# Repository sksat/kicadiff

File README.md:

# kicadiff

Visual diff tool for KiCad projects — see what changed between two
states of a `.kicad_pcb` / `.kicad_sch` / `.kicad_sym` / `.kicad_mod`
file in your browser, or as a markdown report you can paste into a PR.

[日本語版 README](./README.ja.md)

## What you get

- **HTML viewer** with side-by-side / overlay / swipe modes, layer toggles
  for PCBs, page navigation for hierarchical schematics, wheel-to-zoom and
  right-click-drag-to-pan, and an amber tab marker on files / pages whose
  rendered output actually changed.
- **Markdown report** (`--md`) with side-by-side image tables and a
  structural component diff (added / removed / changed by reference
  designator), plus — for PCBs — a `Nets` subsection that lists added /
  removed nets and pads that were rewired (`R1.2: GND → /VCC`). Pad
  transitions to or from the unconnected net are surfaced too
  (`R7.1: (unconnected) → +3V3`). Both legacy (`(net id "name")`) and
  KiCad 10 (`(net "name")`, no top-level net table) shapes are
  supported. Good for PR descriptions and commit messages.
- **Text-only structural diff** (`--text-only`) — fast, no image
  rendering, prints to stdout. Includes the same `Nets` subsection for
  PCBs so routing changes show up in CI logs and grep:

  ```
  blink.kicad_pcb (pcb): +0 -0 ~1 =3
    ~ R1  value: 330 → 470
    Nets: +1 -0 ~2
      + /LED_OUT
      ~ R1.2: GND → /LED_OUT
      ~ R7.1: (unconnected) → +3V3
  ```
- **DRC / ERC violation diff** (`kicadiff check`) — runs design-rule and
  electrical-rule checks on both sides and reports the delta as
  `+N new / -M fixed / =K unchanged`. Exits 1 when the target side
  introduces NEW violations (non-zero on operational failures too —
  missing `kicad-cli`, git errors, JSON parse errors), so it makes a
  good PR gate that fails on regressions while ignoring pre-existing
  findings.

## Requirements

- [`kicad-cli`](https://www.kicad.org/) 9.x or later (rendering engine).
- [Bun](https://bun.sh) — runs the TypeScript CLI directly via shebang.
  Bun also compiles the standalone binary, so no separate Node install
  is needed for any workflow. Standalone binary users skip this.

The render pipeline (SVG → PNG, tri-colour pixel diff highlight) used to
need `rsvg-convert` and ImageMagick; both are now in-process
(`@resvg/resvg-js` for rasterisation, a small custom classifier on top
of `pngjs` for the diff overlay).

## Install

Three ways depending on what's already on your machine:

```sh
# 1. One-shot via Bun's package runner (no install)
bunx kicadiff [args...]

# 2. Global install (puts `kicadiff` on PATH)
pnpm add -g kicadiff
# or with `bun add -g kicadiff` / `npm install -g kicadiff`

# 3. Standalone binary — single file, no Bun runtime needed.
#    Drops `kicadiff` into ~/.local/bin (override with KICADIFF_INSTALL_DIR).
curl -fsSL https://raw.githubusercontent.com/sksat/kicadiff/main/install.sh | sh
```

`kicad-cli` (and `rsvg-convert` / `magick`) are not bundled — install KiCad 9+
first, then pick whichever kicadiff distribution form fits your workflow.

## Usage

`kicadiff` works on the same positional argument shape as `git diff`,
plus a few subcommands when you want to scope to one file type.

```sh
# Project-level diff (cwd, both PCB and schematic, default = index vs working
# tree — same as `git diff`)
kicadiff

# Pass a project root, a .kicad_pro, or any single KiCad file
kicadiff path/to/project/
kicadiff project.kicad_pro
kicadiff project.kicad_pcb

# Staged changes only (same as `git diff --cached` / `git diff --staged`)
kicadiff --cached project/
kicadiff --staged project/             # alias

# Compare arbitrary refs
kicadiff HEAD path/to/project/         # working tree vs HEAD (includes staged)
kicadiff main path/to/project/         # working tree vs main
kicadiff v1.0 v2.0 board.kicad_pcb     # v1.0 vs v2.0
kicadiff main..feat foo.kicad_pcb      # range syntax
kicadiff main -- foo.kicad_pcb         # explicit `--` separator
kicadiff :0 project/                   # explicit index ref (alias: index / staged)

# Subcommands scope to one file type (skip sibling auto-detect)
kicadiff pcb foo.kicad_pcb
kicadiff sch foo.kicad_sch       # alias: schematic
kicadiff sym lib.kicad_sym       # alias: symbol
kicadiff fp foo.kicad_mod        # alias: footprint
kicadiff fp lib.pretty           # whole .pretty/ library

# Output formats
kicadiff project/                       # default: HTML viewer + images
kicadiff project/ --md                  # markdown report + images, no HTML
kicadiff project/ --md --output report.md
kicadiff project/ --md --output -       # markdown to stdout, logs to stderr
kicadiff project/ --text                # also print structural text diff
kicadiff project/ --text-only           # text only, skip rendering (fast)
kicadiff project/ --images-only         # PNGs only, no HTML / markdown

# Custom markdown templates (Mustache subset: {{var}}, {{#section}}…{{/section}},
# {{^inverted}}…{{/inverted}}). Project template sees from_label / to_label /
# file_count / has_changes / files / file_sections. File template sees path /
# type / before_image / after_image / has_both / after_only / before_only /
# added_count / removed_count / changed_count / unchanged_count /
# nets_added / nets_removed / nets_changed (pcb only) /
# has_structural_diff (real component OR net changes) / has_visual_diff (PNGs
# differ) / has_changes (any of the above) / structural_diff (formatted body). Either
# flag is optional; the default template ships built-in.
kicadiff project/ --md --md-template my-report.md.tpl
kicadiff project/ --md --md-file-template my-file.md.tpl

# Auto-open the HTML in VSCode (Live Preview), a browser, etc.
kicadiff project/ --open vscode
kicadiff project/ --open firefox
kicadiff project/ --open=/usr/bin/open  # arbitrary command

# Watch mode — re-render every time an input file changes. Hot reload comes
# from the viewer: VSCode Live Preview / live-server / similar will refresh
# the page automatically once kicadiff overwrites the images. For plain
# file:// browsers, kicadiff injects a tiny image-polling script so the
# rendered images update in place without needing F5.
kicadiff project/ --watch
kicadiff project/ --watch --open vscode

# Other
kicadiff project/ -v                    # verbose summary (full PNG paths)
kicadiff project/ -q                    # suppress summary
kicadiff project/ --no-cache            # bypass the render cache
kicadiff project/ --exit-code           # exit 1 if any change (mirrors `git diff --exit-code`)

# Claude Code PostToolUse hook integration. Reads the hook JSON from
# stdin, renders only when the edited file is .kicad_pcb / .kicad_sch.
# Default: --open vscode (override with --open <target> as usual).
kicadiff hook

# DRC / ERC violation diff — third fast-path mode alongside --text-only.
# Runs `kicad-cli pcb drc` (PCB) / `kicad-cli sch erc` (schematic) on both
# sides and reports the delta as +N new / -M fixed / =K unchanged. Exits 1
# when NEW violations are introduced on the target side; pre-existing
# violations that persist do not fail the gate. Operational failures
# (missing kicad-cli, git errors, JSON parse errors) also produce a
# non-zero exit. Useful as a PR gate that fails only on regressions,
# independent of any visual diff.
kicadiff check                          # PCB+sch in cwd, index vs working
kicadiff check HEAD project/            # working tree vs HEAD
kicadiff check main..feat foo.kicad_pcb # main vs feat, PCB only
```

## Output

By default kicadiff writes to `<repo>/.claude/preview/` (next to the git
root) so the directory is easy to find from the project. Override with
`--output-dir <dir>` for the image directory, and `--output <path>` to
relocate the HTML / markdown file specifically (image paths in the
file get rewritten to be relative to it, so the file stays portable).

The HTML viewer is a single file with the manifest + image references
inline; you can email it, host it as a static asset, or open it
locally with VSCode's Live Preview extension.

## Render cache

Every per-side render is content-addressed and cached under
`$XDG_CACHE_HOME/kicadiff` (or `~/.cache/kicadiff`). Repeat runs
against unchanged content return in ~1 s vs ~5 s cold. Bypass with
`--no-cache` or override the location with `KICADIFF_CACHE_DIR`.

The cache grows monotonically — every kicad-cli version bump and every
content edit adds a new entry, and nothing is evicted automatically.
Inspect and reclaim space with the `cache` subcommand:

```sh
# Show cache directory, entry count, total size, and oldest / newest age
kicadiff cache stats

# Delete entries older than a cutoff (units: s/m/h/d, unit required)
kicadiff cache prune --older-than 30d
kicadiff cache prune --older-than 30d --dry-run    # preview, change nothing

# Wipe the whole cache (recursive rm of the cache root — any stray files
# at the root go too, not just registered entries). `--yes` skips the
# confirmation prompt and is required in non-TTY (CI) environments so
# the prompt can never hang a build. As a safety net, `--all` refuses
# to run unless the cache root contains a `.kicadiff-cache` marker
# (auto-dropped on first cache write and on any `cache stats` /
# read) — that way a misconfigured `KICADIFF_CACHE_DIR` can't silently
# wipe an unrelated directory. For a pre-existing cache from before
# this marker was introduced, run `kicadiff cache stats` once to
# install the marker, then retry `--all`. Use `rm -rf` manually if
# you really mean to delete such a directory.
#
# Note: `cache stats` does NOT recurse into foreign top-level
# directories (anything whose name doesn't match the cache layout's
# 2-char hex bucket pattern). Their bytes are excluded from "Total
# size" — a misconfigured `KICADIFF_CACHE_DIR` (e.g. `$HOME`) won't
# make `stats` walk a huge unrelated tree. `--all` will still wipe
# the entire cache root, so it may reclaim more than `stats` reports.
kicadiff cache prune --all --yes
```

## GitHub Actions

Drop the action into a workflow to render a visual diff for every PR
that touches a KiCad file. The action handles KiCad install, runs
kicadiff, and (opt-in) uploads the rendered images as a build artifact,
writes a job summary with inline before/after images, upserts a sticky
PR comment, and updates a marked section in the PR description.

```yaml
# .github/workflows/kicad-diff.yml
name: KiCad visual diff
on:
  pull_request:
    paths: ["**/*.kicad_pcb", "**/*.kicad_sch"]
permissions:
  contents: read
  pull-requests: write   # only needed for pr-comment / pr-description
jobs:
  diff:
    runs-on: ubuntu-latest
    steps:
      - uses: actions/checkout@v6
        with: { fetch-depth: 0 }
      - uses: sksat/kicadiff@v0.2.0
        with:
          path: hardware/main-board   # default: cwd
          upload-artifact: 'true'
          pr-comment:      'true'
          pr-description:  'true'
```

Job summary embeds combined PNGs as base64 data URIs (no extra hosting
needed) up to a 1 MiB cap; if a project's images would overflow, the
action drops the rest, emits `::warning::`, and links to the artifact
for the full set. PR comment / description are kept text-only and link
to the artifact for images.

`install-kicadiff: bunx` (default) pulls the latest published kicadiff
on demand; pin a version with `install-kicadiff: <semver>`. Pre-installed
on PATH? Use `install-kicadiff: skip`.

## More

- `DESIGN.md` — architecture, render pipeline, cache key shape,
  manifest schema, viewer mode semantics
- `examples/blink/` — minimal KiCad project used as the test fixture
  and a usable starting point. Ships with a `.claude/settings.json`
  PostToolUse hook (`kicadiff hook`) that re-renders the diff every
  time a `.kicad_pcb` / `.kicad_sch` is Edited / Written.
- `examples/mcu-board/` — a more realistic small-board layout: an
  8-pin MCU stand-in with the usual stuff around it (5 V → 3.3 V
  AMS1117 LDO, decoupling caps, reset switch with pull-up, status
  LED, and a 6-pin programming/breakout header). Hierarchical
  schematic — root for the power chain and MCU itself,
  `peripherals.kicad_sch` sub-sheet for the reset/LED/header — so
  the per-page tabs in the viewer have something to switch between.

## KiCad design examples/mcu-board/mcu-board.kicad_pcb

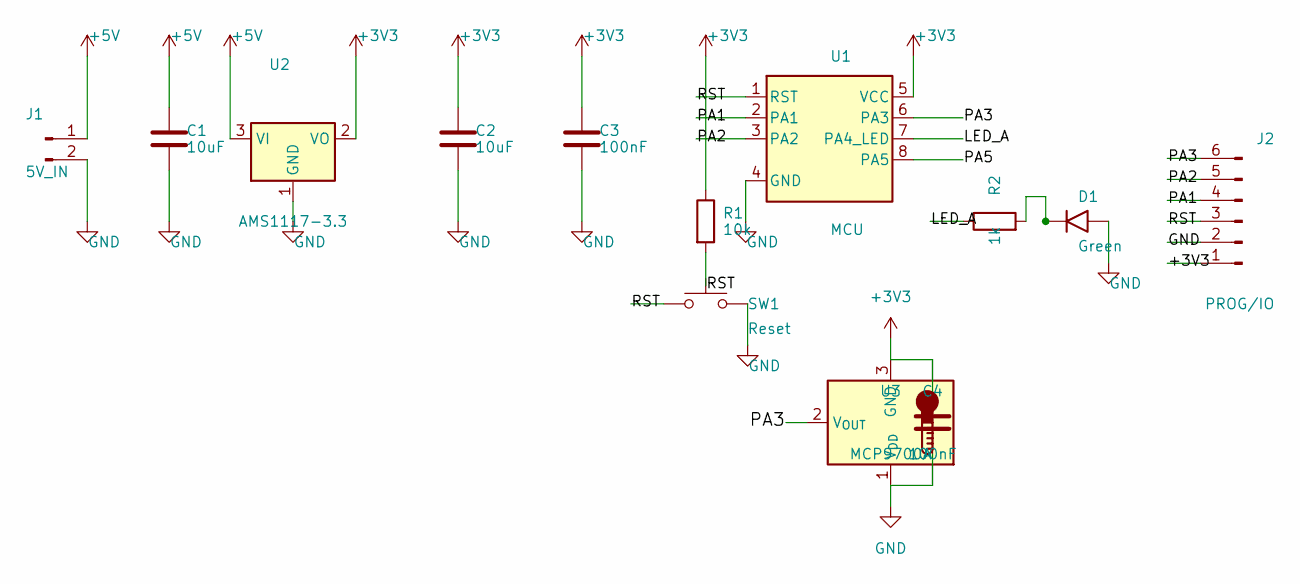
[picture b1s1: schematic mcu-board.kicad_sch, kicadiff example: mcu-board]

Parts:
C1, C2: 10uF; C_0805_2012Metric
C3, C4: 100nF; C_0805_2012Metric
D1: Green; LED_0805_2012Metric
J1: 5V_IN; PinHeader_1x02_P2.54mm_Vertical
J2: PROG/IO; PinHeader_1x06_P2.54mm_Vertical
R1: 10k; R_0805_2012Metric
R2: 1k; R_0805_2012Metric
SW1: Reset; SW_SPST_TL3342
U1: MCU; SOIC-8_3.9x4.9mm_P1.27mm
U2: AMS1117-3.3; SOT-223-3_TabPin2
U3: MCP9700A; SOT-23

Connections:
+3V3: C2.1, C3.1, C4.1, J2.1, R1.1, U1.5 (VCC), U2.2 (VO), U3.1
+5V: C1.1, J1.1, U2.3 (VI)
/LED_A: R2.1, U1.7 (PA4_LED)
/PA1: J2.4, U1.2 (PA1)
/PA2: J2.5, U1.3 (PA2)
/PA3: J2.6, U1.6 (PA3), U3.2
/PA5: U1.8 (PA5)
/RST: J2.3, R1.2, SW1.1, U1.1 (RST)
GND: C1.2, C2.2, C3.2, C4.2, D1.2 (A), J1.2, J2.2, SW1.2, U1.4 (GND), U2.1 (GND), U3.3
unnamed: D1.1 (K), R2.2

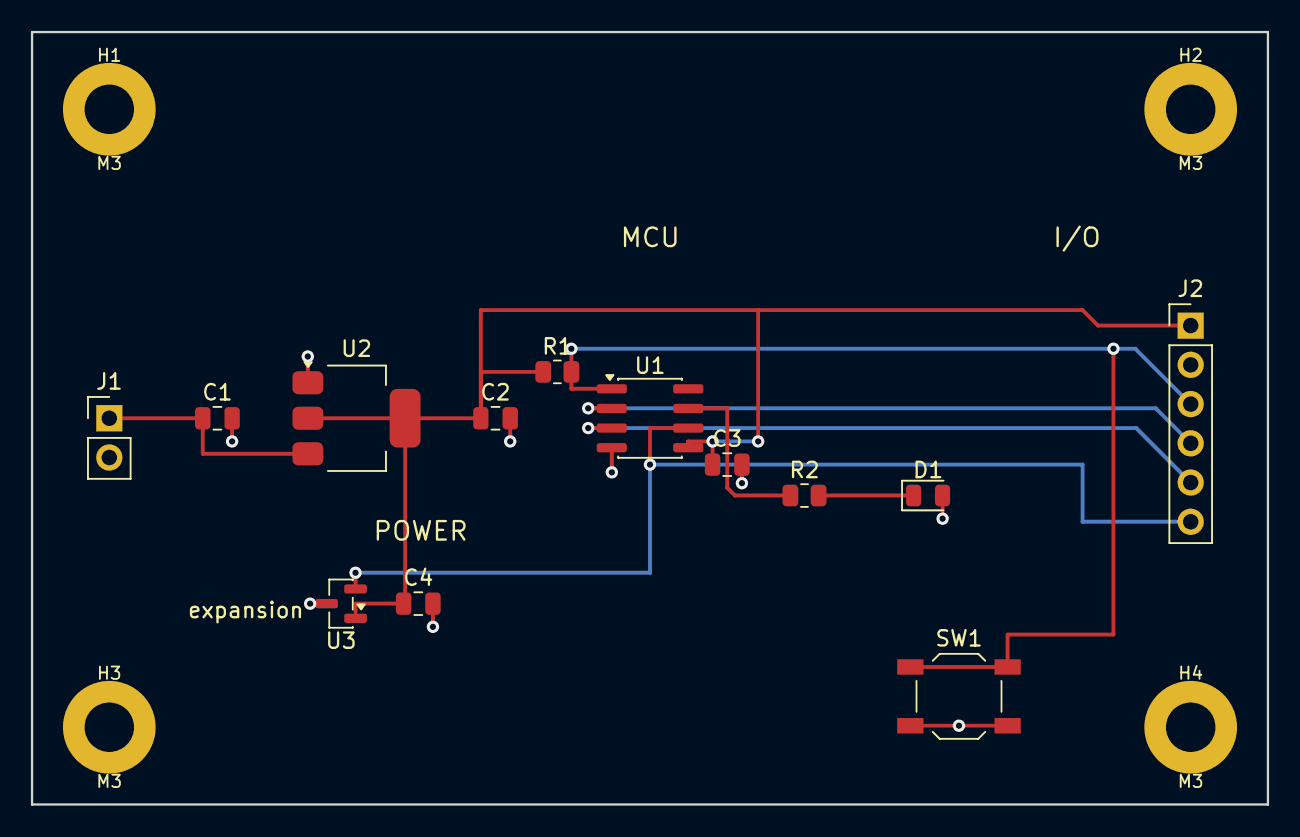
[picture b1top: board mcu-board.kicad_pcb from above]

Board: 2 copper layers, 80.0 x 50.0 mm, 17 parts (0 on the bottom side), 9 nets.

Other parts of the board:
H1, H2, H3, H4: M3; MountingHole_3.2mm_M3

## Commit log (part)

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2026-05-10 chore(deps): pin dependencies
2026-05-10 chore(kicadiff): update preview images
2026-05-12 chore(deps): update pnpm to v10.33.4
2026-05-18 chore(deps): update pnpm to v11
2026-05-18 chore(deps): update actions/upload-artifact action to v7
2026-05-18 chore(deps): update pnpm/action-setup action to v6.0.8
2026-05-19 chore(deps): update dependency @playwright/test to v1.60.0
2026-05-21 chore(deps): update pnpm to v11.2.2
2026-05-24 chore(deps): update pnpm to v11.3.0
2026-06-26 chore(deps): update actions/cache action to v5.1.0
2026-06-26 chore(deps): update actions/cache action to v6
